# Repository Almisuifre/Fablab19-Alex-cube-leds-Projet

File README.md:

# Fablab19-Alex-cube-leds-Projet
Projet du FbLab19 Cube de leds

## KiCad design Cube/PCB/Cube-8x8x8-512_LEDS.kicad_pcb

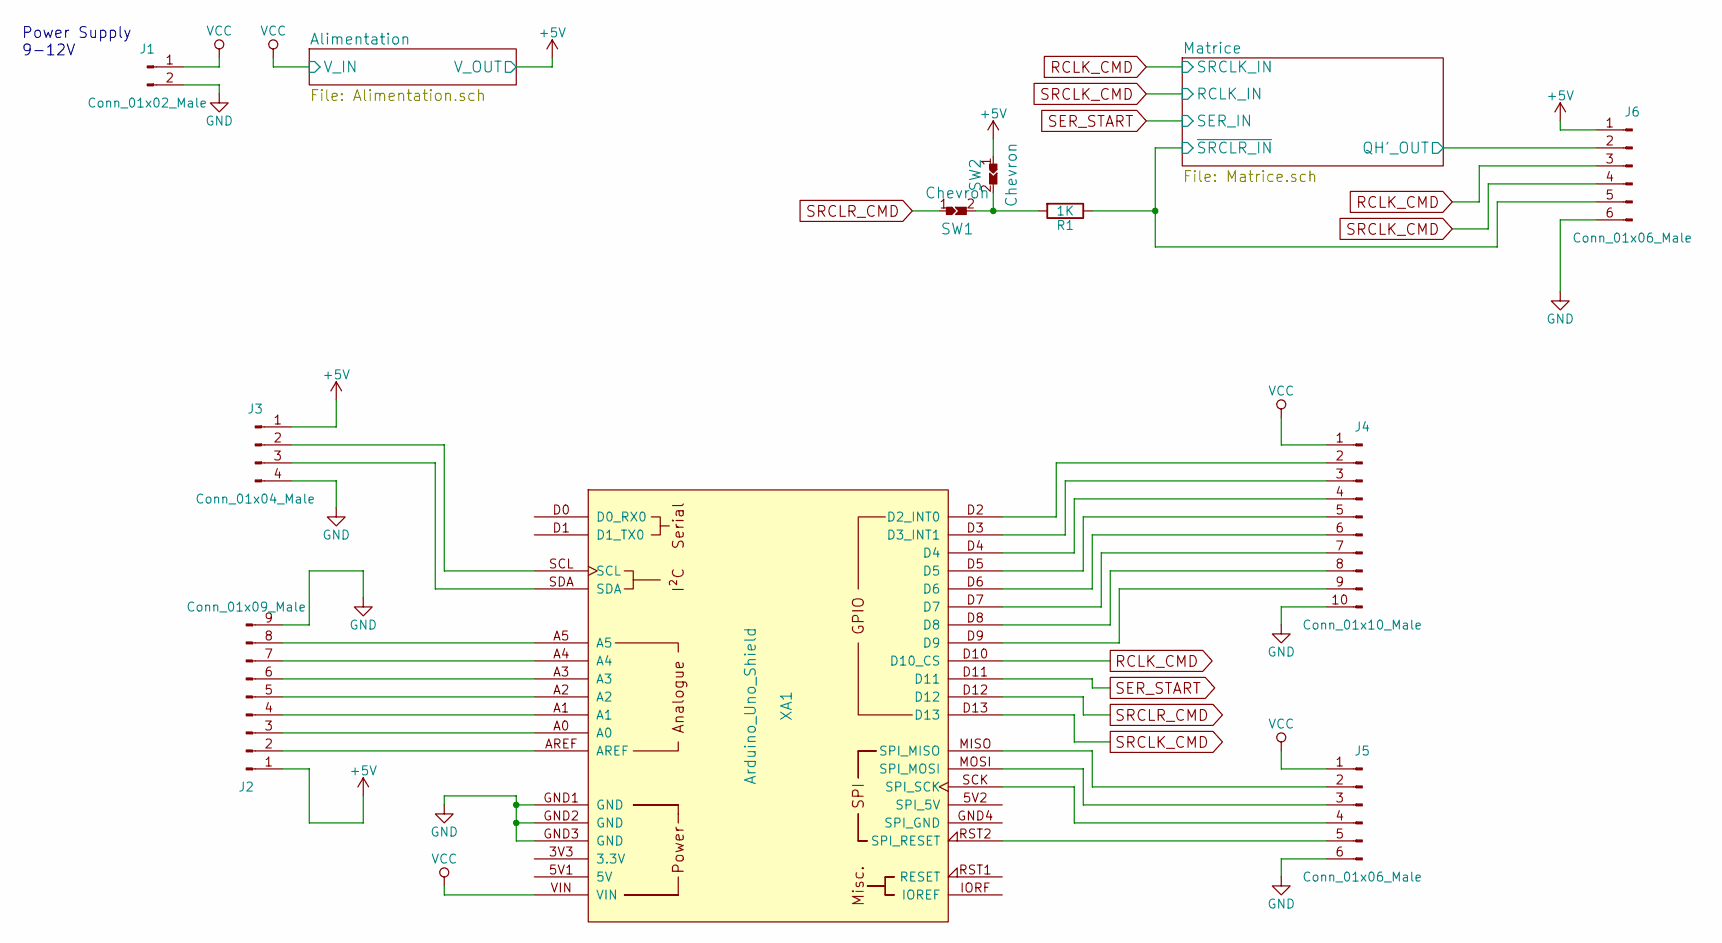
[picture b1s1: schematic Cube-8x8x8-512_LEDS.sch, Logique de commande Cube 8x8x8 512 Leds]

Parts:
J1: Conn_01x02_Male; Connect-2pin
J2: Conn_01x09_Male; Connect-9pin
J3: Conn_01x04_Male; Connect-4pin
J4: Conn_01x10_Male; Connect-10pin
J5, J6: Conn_01x06_Male; Connect-6pin
R1: 1K; R_Axial_Long6.3mm_Dia2.5mm_Pas15.24mm_Horizontal
SW1, SW2: Chevron; Chevron-E1
XA1: Arduino_Uno_Shield

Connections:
+5V: J2.1, J3.1, J6.1, SW2.1; also elsewhere on the board
/Matrice/QH'_OUT: J6.2; also elsewhere on the board
/Matrice/~SRCLR_IN: J6.5, R1.1; also elsewhere on the board
GND: J1.2, J2.9, J3.4, J4.10, J5.6, J6.6, XA1.GND1 (GND), XA1.GND2 (GND), XA1.GND3 (GND); also elsewhere on the board
unnamed: J2.2, XA1.AREF
unnamed: J2.3, XA1.A0
unnamed: J2.4, XA1.A1
unnamed: J2.5, XA1.A2
unnamed: J2.6, XA1.A3
unnamed: J2.7, XA1.A4
unnamed: J2.8, XA1.A5
unnamed: J3.2, XA1.SCL
unnamed: J3.3, XA1.SDA
unnamed: J4.2, XA1.D2 (D2_INT0)
unnamed: J4.3, XA1.D3 (D3_INT1)
unnamed: J4.4, XA1.D4
unnamed: J4.5, XA1.D5
unnamed: J4.6, XA1.D6
unnamed: J4.7, XA1.D7
unnamed: J4.8, XA1.D8
unnamed: J4.9, XA1.D9
unnamed: J5.2, XA1.MISO (SPI_MISO)
unnamed: J5.3, XA1.MOSI (SPI_MOSI)
unnamed: J5.4, XA1.SCK (SPI_SCK)
unnamed: J5.5, XA1.RST2 (SPI_RESET)
unnamed: R1.2, SW1.2, SW2.2
RCLK_CMD: J6.3, XA1.D10 (D10_CS); also elsewhere on the board
SER_START: XA1.D11; also elsewhere on the board
SRCLK_CMD: J6.4, XA1.D13; also elsewhere on the board
SRCLR_CMD: SW1.1, XA1.D12
VCC: J1.1, J4.1, J5.1, XA1.VIN; also elsewhere on the board

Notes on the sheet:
Power Supply 9-12V

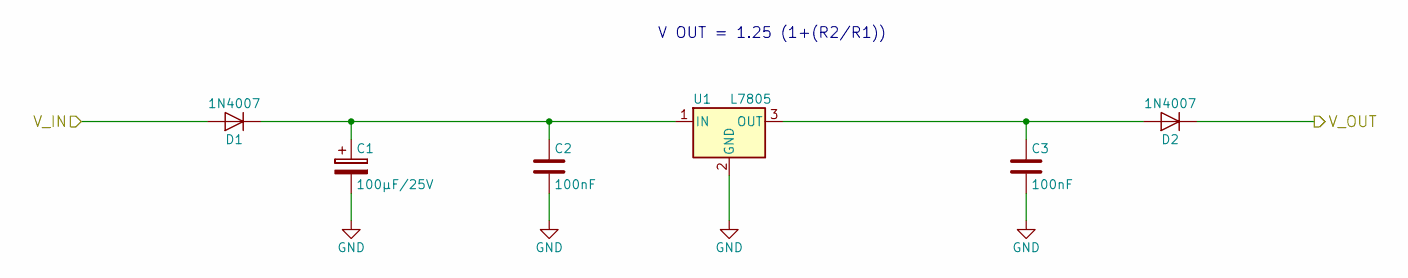
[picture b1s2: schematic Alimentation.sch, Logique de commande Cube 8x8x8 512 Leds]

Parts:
C1: 100µF/25V; CP_Radial_Dia8.0mm_Pas3.50mm
C2, C3: 100nF; C-P_5.08-L_7.5-H_6-P_2.5
D1, D2: 1N4007; D_DO-41_Pas12.70mm_Horizontal
U1: L7805; TO-220_Vertical

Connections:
+5V: D2.1 (K); also elsewhere on the board
GND: C1.2, C2.2, C3.2, U1.2 (GND); also elsewhere on the board
unnamed: C1.1, C2.1, D1.1 (K), U1.1 (IN)
unnamed: C3.1, D2.2 (A), U1.3 (OUT)
VCC: D1.2 (A); also elsewhere on the board

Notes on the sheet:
V OUT = 1.25 (1+(R2/R1))

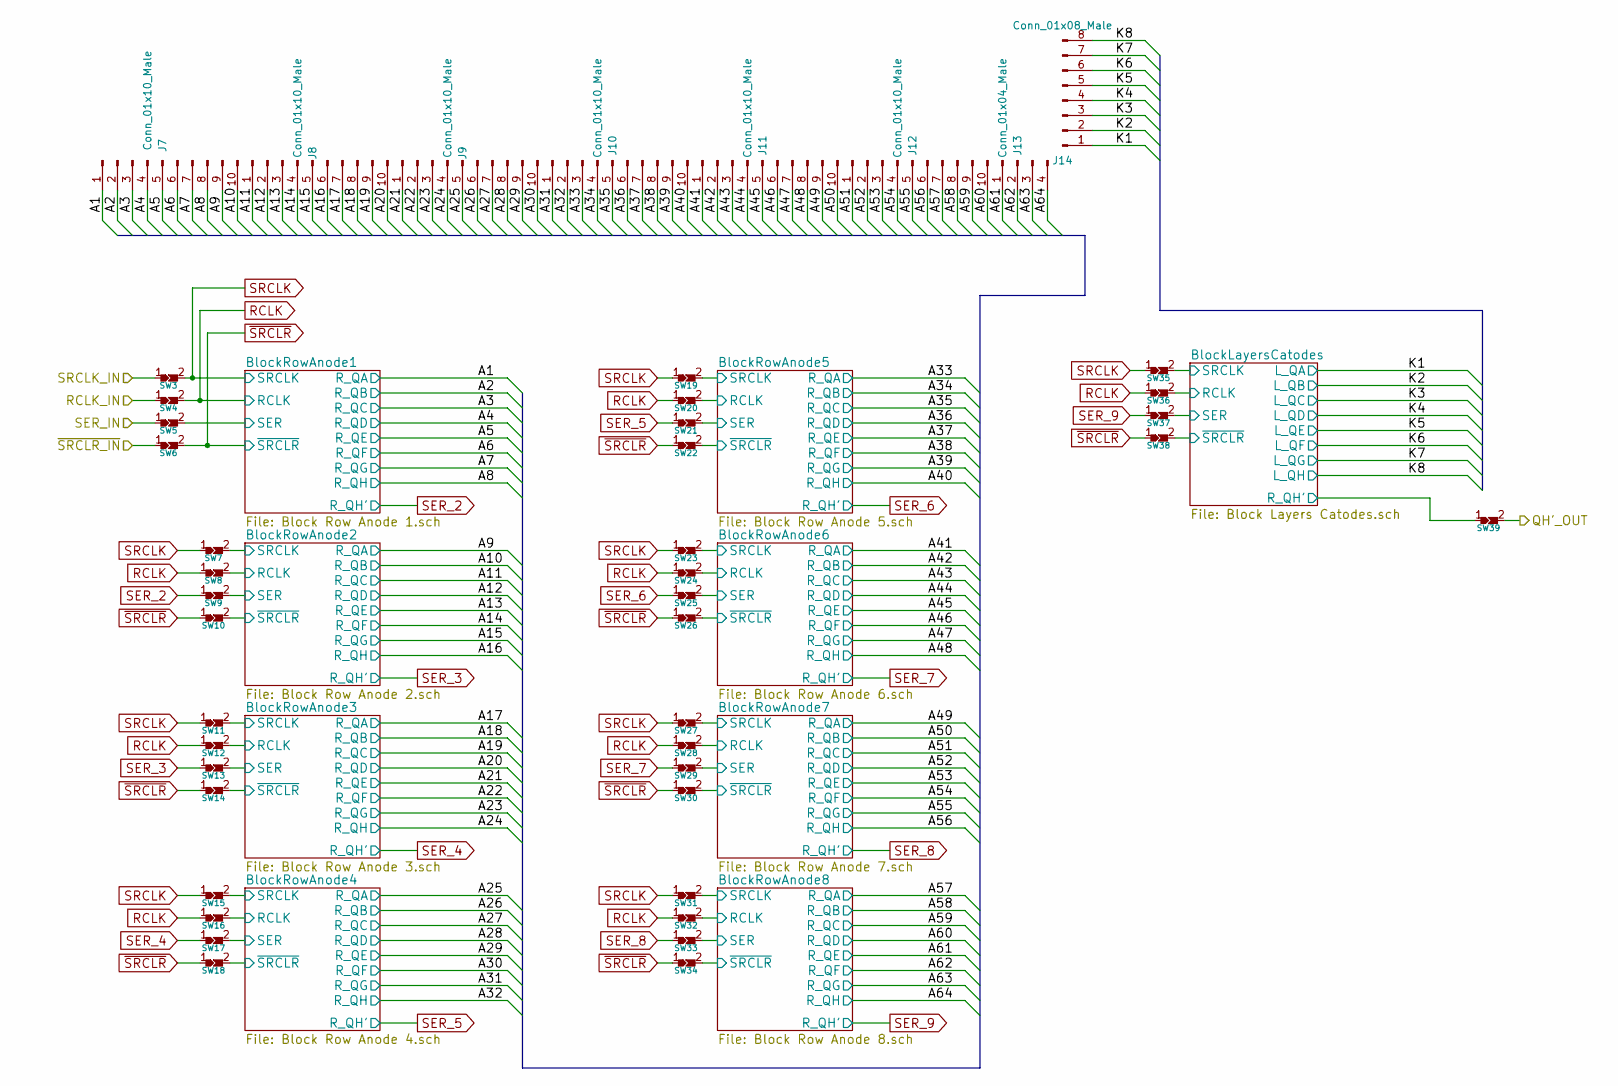
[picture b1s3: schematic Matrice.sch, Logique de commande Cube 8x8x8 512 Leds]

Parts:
J7, J8, J9, J10, J11, J12: Conn_01x10_Male; Connect-10pin
J13: Conn_01x04_Male; Connect-4pin
J14: Conn_01x08_Male; Connect-8pin
SW3, SW4, SW5, SW6, SW7, SW8, SW9, SW10, SW11, SW12, SW13, SW14, SW15, SW16, SW17, SW18, SW19, SW20, SW21, SW22, SW23, SW24, SW25, SW26, SW27, SW28, SW29, SW30, SW31, SW32, SW33, SW34, SW35, SW36, SW37, SW38, SW39: Chevron; Chevron-E1

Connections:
/Matrice/A1: J7.1; also elsewhere on the board
/Matrice/A2: J7.2; also elsewhere on the board
/Matrice/A3: J7.3; also elsewhere on the board
/Matrice/A4: J7.4; also elsewhere on the board
/Matrice/A5: J7.5; also elsewhere on the board
/Matrice/A6: J7.6; also elsewhere on the board
/Matrice/A7: J7.7; also elsewhere on the board
/Matrice/A8: J7.8; also elsewhere on the board
/Matrice/A9: J7.9; also elsewhere on the board
/Matrice/A10: J7.10; also elsewhere on the board
/Matrice/A11: J8.1; also elsewhere on the board
/Matrice/A12: J8.2; also elsewhere on the board
/Matrice/A13: J8.3; also elsewhere on the board
/Matrice/A14: J8.4; also elsewhere on the board
/Matrice/A15: J8.5; also elsewhere on the board
/Matrice/A16: J8.6; also elsewhere on the board
/Matrice/A17: J8.7; also elsewhere on the board
/Matrice/A18: J8.8; also elsewhere on the board
/Matrice/A19: J8.9; also elsewhere on the board
/Matrice/A20: J8.10; also elsewhere on the board
/Matrice/A21: J9.1; also elsewhere on the board
/Matrice/A22: J9.2; also elsewhere on the board
/Matrice/A23: J9.3; also elsewhere on the board
/Matrice/A24: J9.4; also elsewhere on the board
/Matrice/A25: J9.5; also elsewhere on the board
/Matrice/A26: J9.6; also elsewhere on the board
/Matrice/A27: J9.7; also elsewhere on the board
/Matrice/A28: J9.8; also elsewhere on the board
/Matrice/A29: J9.9; also elsewhere on the board
/Matrice/A30: J9.10; also elsewhere on the board
/Matrice/A31: J10.1; also elsewhere on the board
/Matrice/A32: J10.2; also elsewhere on the board
/Matrice/A33: J10.3; also elsewhere on the board
/Matrice/A34: J10.4; also elsewhere on the board
/Matrice/A35: J10.5; also elsewhere on the board
/Matrice/A36: J10.6; also elsewhere on the board
/Matrice/A37: J10.7; also elsewhere on the board
/Matrice/A38: J10.8; also elsewhere on the board
/Matrice/A39: J10.9; also elsewhere on the board
/Matrice/A40: J10.10; also elsewhere on the board
/Matrice/A41: J11.1; also elsewhere on the board
/Matrice/A42: J11.2; also elsewhere on the board
/Matrice/A43: J11.3; also elsewhere on the board
/Matrice/A44: J11.4; also elsewhere on the board
/Matrice/A45: J11.5; also elsewhere on the board
/Matrice/A46: J11.6; also elsewhere on the board
/Matrice/A47: J11.7; also elsewhere on the board
/Matrice/A48: J11.8; also elsewhere on the board
/Matrice/A49: J11.9; also elsewhere on the board
/Matrice/A50: J11.10; also elsewhere on the board
/Matrice/A51: J12.1; also elsewhere on the board
/Matrice/A52: J12.2; also elsewhere on the board
/Matrice/A53: J12.3; also elsewhere on the board
/Matrice/A54: J12.4; also elsewhere on the board
/Matrice/A55: J12.5; also elsewhere on the board
/Matrice/A56: J12.6; also elsewhere on the board
/Matrice/A57: J12.7; also elsewhere on the board
/Matrice/A58: J12.8; also elsewhere on the board
/Matrice/A59: J12.9; also elsewhere on the board
/Matrice/A60: J12.10; also elsewhere on the board
/Matrice/A61: J13.1; also elsewhere on the board
/Matrice/A62: J13.2; also elsewhere on the board
/Matrice/A63: J13.3; also elsewhere on the board
/Matrice/A64: J13.4; also elsewhere on the board
/Matrice/BlockLayersCatodes/RCLK: SW36.2; also elsewhere on the board
/Matrice/BlockLayersCatodes/R_QH': SW39.1; also elsewhere on the board
/Matrice/BlockLayersCatodes/SER: SW37.2; also elsewhere on the board
/Matrice/BlockLayersCatodes/SRCLK: SW35.2; also elsewhere on the board
/Matrice/BlockLayersCatodes/~SRCLR: SW38.2; also elsewhere on the board
/Matrice/BlockRowAnode1/SER: SW5.2; also elsewhere on the board
/Matrice/BlockRowAnode2/RCLK: SW8.2; also elsewhere on the board
/Matrice/BlockRowAnode2/SER: SW9.2; also elsewhere on the board
/Matrice/BlockRowAnode2/SRCLK: SW7.2; also elsewhere on the board
/Matrice/BlockRowAnode2/~SRCLR: SW10.2; also elsewhere on the board
/Matrice/BlockRowAnode3/RCLK: SW12.2; also elsewhere on the board
/Matrice/BlockRowAnode3/SER: SW13.2; also elsewhere on the board
/Matrice/BlockRowAnode3/SRCLK: SW11.2; also elsewhere on the board
/Matrice/BlockRowAnode3/~SRCLR: SW14.2; also elsewhere on the board
/Matrice/BlockRowAnode4/RCLK: SW16.2; also elsewhere on the board
/Matrice/BlockRowAnode4/SER: SW17.2; also elsewhere on the board
/Matrice/BlockRowAnode4/SRCLK: SW15.2; also elsewhere on the board
/Matrice/BlockRowAnode4/~SRCLR: SW18.2; also elsewhere on the board
/Matrice/BlockRowAnode5/RCLK: SW20.2; also elsewhere on the board
/Matrice/BlockRowAnode5/SER: SW21.2; also elsewhere on the board
/Matrice/BlockRowAnode5/SRCLK: SW19.2; also elsewhere on the board
/Matrice/BlockRowAnode5/~SRCLR: SW22.2; also elsewhere on the board
/Matrice/BlockRowAnode6/RCLK: SW24.2; also elsewhere on the board
/Matrice/BlockRowAnode6/SER: SW25.2; also elsewhere on the board
/Matrice/BlockRowAnode6/SRCLK: SW23.2; also elsewhere on the board
/Matrice/BlockRowAnode6/~SRCLR: SW26.2; also elsewhere on the board
/Matrice/BlockRowAnode7/RCLK: SW28.2; also elsewhere on the board
/Matrice/BlockRowAnode7/SER: SW29.2; also elsewhere on the board
/Matrice/BlockRowAnode7/SRCLK: SW27.2; also elsewhere on the board
/Matrice/BlockRowAnode7/~SRCLR: SW30.2; also elsewhere on the board
/Matrice/BlockRowAnode8/RCLK: SW32.2; also elsewhere on the board
/Matrice/BlockRowAnode8/SER: SW33.2; also elsewhere on the board
/Matrice/BlockRowAnode8/SRCLK: SW31.2; also elsewhere on the board
/Matrice/BlockRowAnode8/~SRCLR: SW34.2; also elsewhere on the board
/Matrice/K1: J14.1; also elsewhere on the board
/Matrice/K2: J14.2; also elsewhere on the board
/Matrice/K3: J14.3; also elsewhere on the board
/Matrice/K4: J14.4; also elsewhere on the board
/Matrice/K5: J14.5; also elsewhere on the board
/Matrice/K6: J14.6; also elsewhere on the board
/Matrice/K7: J14.7; also elsewhere on the board
/Matrice/K8: J14.8; also elsewhere on the board
/Matrice/QH'_OUT: SW39.2; also elsewhere on the board
/Matrice/~SRCLR_IN: SW6.1; also elsewhere on the board
RCLK: SW4.2, SW8.1, SW12.1, SW16.1, SW20.1, SW24.1, SW28.1, SW32.1, SW36.1; also elsewhere on the board
RCLK_CMD: SW3.1; also elsewhere on the board
SER_2: SW9.1; also elsewhere on the board
SER_3: SW13.1; also elsewhere on the board
SER_4: SW17.1; also elsewhere on the board
SER_5: SW21.1; also elsewhere on the board
SER_6: SW25.1; also elsewhere on the board
SER_7: SW29.1; also elsewhere on the board
SER_8: SW33.1; also elsewhere on the board
SER_9: SW37.1; also elsewhere on the board
SER_START: SW5.1; also elsewhere on the board
SRCLK: SW3.2, SW7.1, SW11.1, SW15.1, SW19.1, SW23.1, SW27.1, SW31.1, SW35.1; also elsewhere on the board
SRCLK_CMD: SW4.1; also elsewhere on the board
~SRCLR: SW6.2, SW10.1, SW14.1, SW18.1, SW22.1, SW26.1, SW30.1, SW34.1, SW38.1; also elsewhere on the board

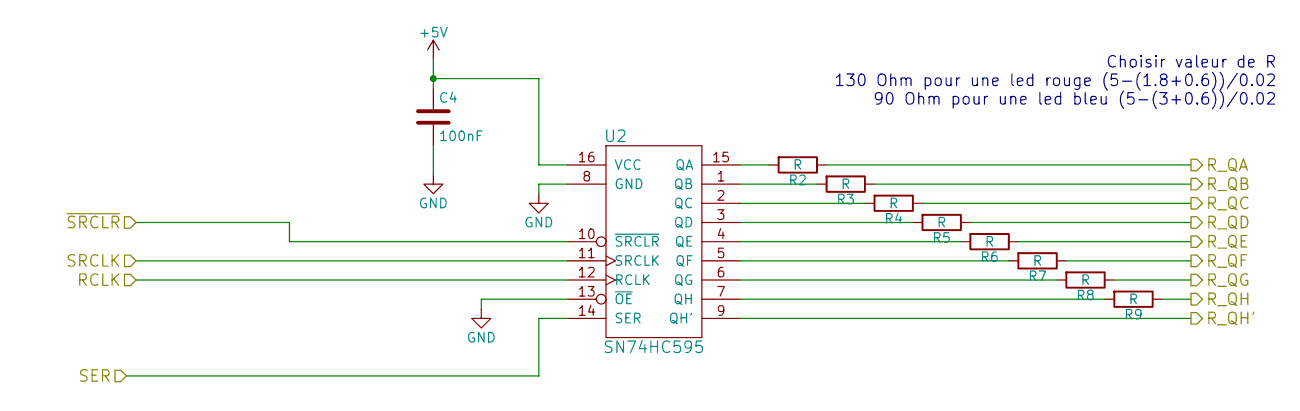
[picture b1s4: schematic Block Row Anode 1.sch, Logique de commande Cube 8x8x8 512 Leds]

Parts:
C4: 100nF; C-P_5.08-L_7.5-H_6-P_2.5
R2, R3, R4, R5, R6, R7, R8, R9: R; R_Axial_Long6.3mm_Dia2.5mm_Pas15.24mm_Horizontal
U2: SN74HC595; DIP-16_W7.62mm_LongPads

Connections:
+5V: C4.1, U2.16 (VCC); also elsewhere on the board
/Matrice/A1: R2.1; also elsewhere on the board
/Matrice/A2: R3.1; also elsewhere on the board
/Matrice/A3: R4.1; also elsewhere on the board
/Matrice/A4: R5.1; also elsewhere on the board
/Matrice/A5: R6.1; also elsewhere on the board
/Matrice/A6: R7.1; also elsewhere on the board
/Matrice/A7: R8.1; also elsewhere on the board
/Matrice/A8: R9.1; also elsewhere on the board
/Matrice/BlockRowAnode1/SER: U2.14 (SER); also elsewhere on the board
GND: C4.2, U2.8 (GND), U2.13 (~OE); also elsewhere on the board
unnamed: R2.2, U2.15 (QA)
unnamed: R3.2, U2.1 (QB)
unnamed: R4.2, U2.2 (QC)
unnamed: R5.2, U2.3 (QD)
unnamed: R6.2, U2.4 (QE)
unnamed: R7.2, U2.5 (QF)
unnamed: R8.2, U2.6 (QG)
unnamed: R9.2, U2.7 (QH)
RCLK: U2.12 (RCLK); also elsewhere on the board
SER_2: U2.9 (QH'); also elsewhere on the board
SRCLK: U2.11 (SRCLK); also elsewhere on the board
~SRCLR: U2.10 (~SRCLR); also elsewhere on the board

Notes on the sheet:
Choisir valeur de R 130 Ohm pour une led rouge (5-(1.8+0.6))/0.02 90 Ohm pour une led bleu (5-(3+0.6))/0.02

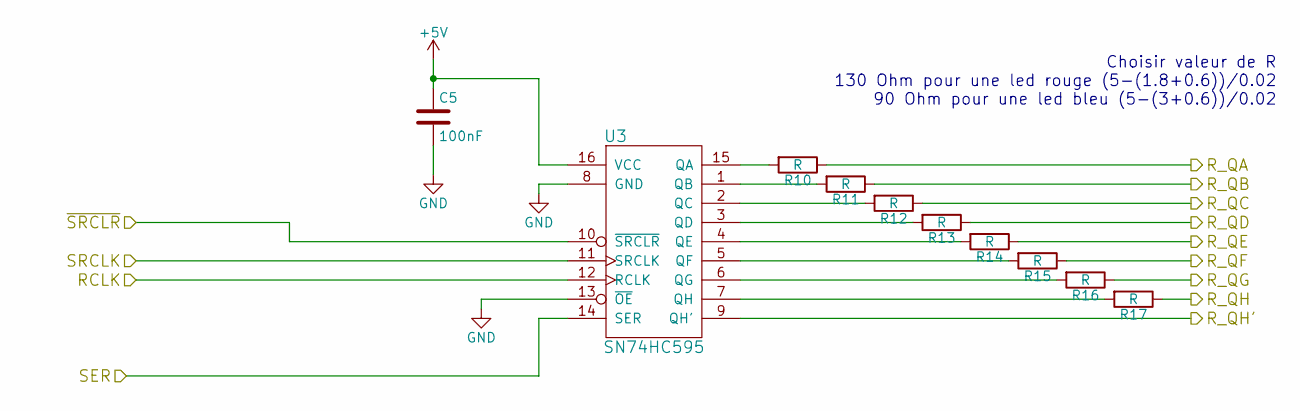
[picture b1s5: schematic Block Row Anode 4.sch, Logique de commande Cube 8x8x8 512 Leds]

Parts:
C5: 100nF; C-P_5.08-L_7.5-H_6-P_2.5
R10, R11, R12, R13, R14, R15, R16, R17: R; R_Axial_Long6.3mm_Dia2.5mm_Pas15.24mm_Horizontal
U3: SN74HC595; DIP-16_W7.62mm_LongPads

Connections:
+5V: C5.1, U3.16 (VCC); also elsewhere on the board
/Matrice/A25: R10.1; also elsewhere on the board
/Matrice/A26: R11.1; also elsewhere on the board
/Matrice/A27: R12.1; also elsewhere on the board
/Matrice/A28: R13.1; also elsewhere on the board
/Matrice/A29: R14.1; also elsewhere on the board
/Matrice/A30: R15.1; also elsewhere on the board
/Matrice/A31: R16.1; also elsewhere on the board
/Matrice/A32: R17.1; also elsewhere on the board
/Matrice/BlockRowAnode4/RCLK: U3.12 (RCLK); also elsewhere on the board
/Matrice/BlockRowAnode4/SER: U3.14 (SER); also elsewhere on the board
/Matrice/BlockRowAnode4/SRCLK: U3.11 (SRCLK); also elsewhere on the board
/Matrice/BlockRowAnode4/~SRCLR: U3.10 (~SRCLR); also elsewhere on the board
GND: C5.2, U3.8 (GND), U3.13 (~OE); also elsewhere on the board
unnamed: R10.2, U3.15 (QA)
unnamed: R11.2, U3.1 (QB)
unnamed: R12.2, U3.2 (QC)
unnamed: R13.2, U3.3 (QD)
unnamed: R14.2, U3.4 (QE)
unnamed: R15.2, U3.5 (QF)
unnamed: R16.2, U3.6 (QG)
unnamed: R17.2, U3.7 (QH)
SER_5: U3.9 (QH'); also elsewhere on the board

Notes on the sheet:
Choisir valeur de R 130 Ohm pour une led rouge (5-(1.8+0.6))/0.02 90 Ohm pour une led bleu (5-(3+0.6))/0.02

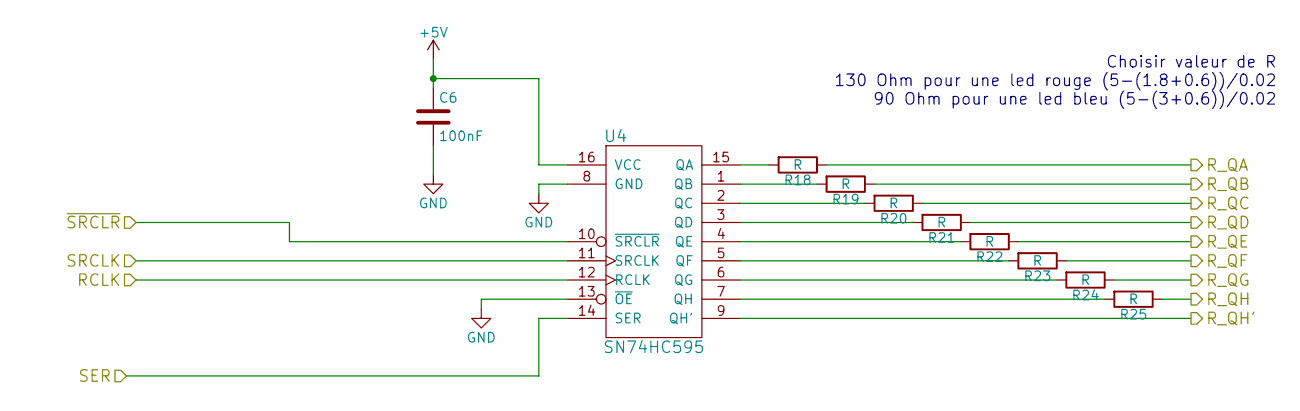
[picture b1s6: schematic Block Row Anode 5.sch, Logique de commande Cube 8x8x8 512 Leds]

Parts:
C6: 100nF; C-P_5.08-L_7.5-H_6-P_2.5
R18, R19, R20, R21, R22, R23, R24, R25: R; R_Axial_Long6.3mm_Dia2.5mm_Pas15.24mm_Horizontal
U4: SN74HC595; DIP-16_W7.62mm_LongPads

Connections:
+5V: C6.1, U4.16 (VCC); also elsewhere on the board
/Matrice/A33: R18.1; also elsewhere on the board
/Matrice/A34: R19.1; also elsewhere on the board
/Matrice/A35: R20.1; also elsewhere on the board
/Matrice/A36: R21.1; also elsewhere on the board
/Matrice/A37: R22.1; also elsewhere on the board
/Matrice/A38: R23.1; also elsewhere on the board
/Matrice/A39: R24.1; also elsewhere on the board
/Matrice/A40: R25.1; also elsewhere on the board
/Matrice/BlockRowAnode5/RCLK: U4.12 (RCLK); also elsewhere on the board
/Matrice/BlockRowAnode5/SER: U4.14 (SER); also elsewhere on the board
/Matrice/BlockRowAnode5/SRCLK: U4.11 (SRCLK); also elsewhere on the board
/Matrice/BlockRowAnode5/~SRCLR: U4.10 (~SRCLR); also elsewhere on the board
GND: C6.2, U4.8 (GND), U4.13 (~OE); also elsewhere on the board
unnamed: R18.2, U4.15 (QA)
unnamed: R19.2, U4.1 (QB)
unnamed: R20.2, U4.2 (QC)
unnamed: R21.2, U4.3 (QD)
unnamed: R22.2, U4.4 (QE)
unnamed: R23.2, U4.5 (QF)
unnamed: R24.2, U4.6 (QG)
unnamed: R25.2, U4.7 (QH)
SER_6: U4.9 (QH'); also elsewhere on the board

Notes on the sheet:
Choisir valeur de R 130 Ohm pour une led rouge (5-(1.8+0.6))/0.02 90 Ohm pour une led bleu (5-(3+0.6))/0.02

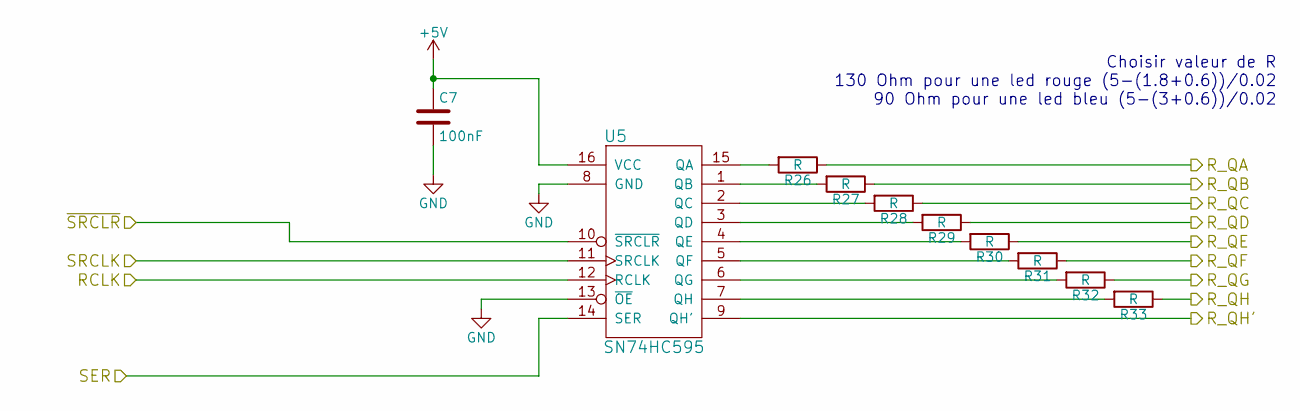
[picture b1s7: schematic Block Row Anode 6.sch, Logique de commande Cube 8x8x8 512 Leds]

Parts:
C7: 100nF; C-P_5.08-L_7.5-H_6-P_2.5
R26, R27, R28, R29, R30, R31, R32, R33: R; R_Axial_Long6.3mm_Dia2.5mm_Pas15.24mm_Horizontal
U5: SN74HC595; DIP-16_W7.62mm_LongPads

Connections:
+5V: C7.1, U5.16 (VCC); also elsewhere on the board
/Matrice/A41: R26.1; also elsewhere on the board
/Matrice/A42: R27.1; also elsewhere on the board
/Matrice/A43: R28.1; also elsewhere on the board
/Matrice/A44: R29.1; also elsewhere on the board
/Matrice/A45: R30.1; also elsewhere on the board
/Matrice/A46: R31.1; also elsewhere on the board
/Matrice/A47: R32.1; also elsewhere on the board
/Matrice/A48: R33.1; also elsewhere on the board
/Matrice/BlockRowAnode6/RCLK: U5.12 (RCLK); also elsewhere on the board
/Matrice/BlockRowAnode6/SER: U5.14 (SER); also elsewhere on the board
/Matrice/BlockRowAnode6/SRCLK: U5.11 (SRCLK); also elsewhere on the board
/Matrice/BlockRowAnode6/~SRCLR: U5.10 (~SRCLR); also elsewhere on the board
GND: C7.2, U5.8 (GND), U5.13 (~OE); also elsewhere on the board
unnamed: R26.2, U5.15 (QA)
unnamed: R27.2, U5.1 (QB)
unnamed: R28.2, U5.2 (QC)
unnamed: R29.2, U5.3 (QD)
unnamed: R30.2, U5.4 (QE)
unnamed: R31.2, U5.5 (QF)
unnamed: R32.2, U5.6 (QG)
unnamed: R33.2, U5.7 (QH)
SER_7: U5.9 (QH'); also elsewhere on the board

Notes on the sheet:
Choisir valeur de R 130 Ohm pour une led rouge (5-(1.8+0.6))/0.02 90 Ohm pour une led bleu (5-(3+0.6))/0.02

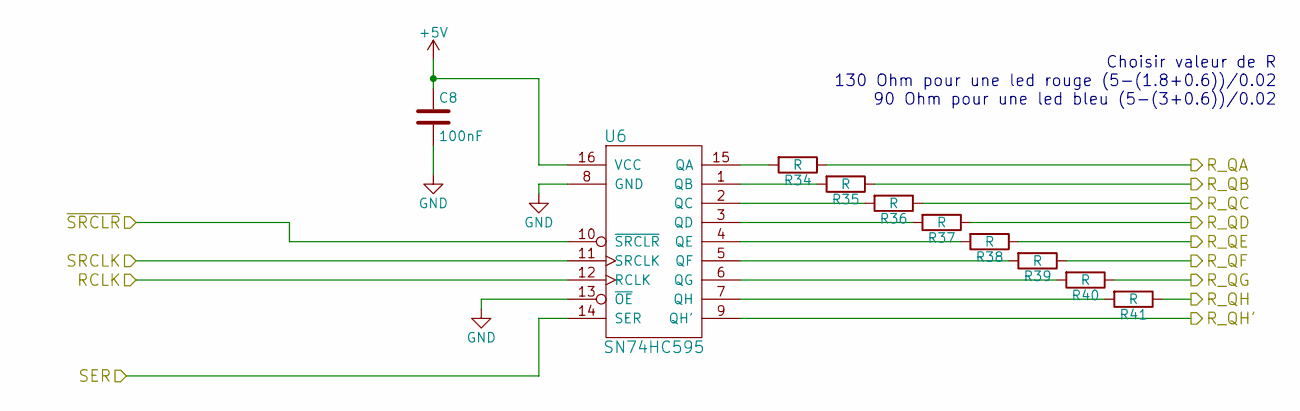
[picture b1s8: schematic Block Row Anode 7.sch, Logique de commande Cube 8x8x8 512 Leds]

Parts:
C8: 100nF; C-P_5.08-L_7.5-H_6-P_2.5
R34, R35, R36, R37, R38, R39, R40, R41: R; R_Axial_Long6.3mm_Dia2.5mm_Pas15.24mm_Horizontal
U6: SN74HC595; DIP-16_W7.62mm_LongPads

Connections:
+5V: C8.1, U6.16 (VCC); also elsewhere on the board
/Matrice/A49: R34.1; also elsewhere on the board
/Matrice/A50: R35.1; also elsewhere on the board
/Matrice/A51: R36.1; also elsewhere on the board
/Matrice/A52: R37.1; also elsewhere on the board
/Matrice/A53: R38.1; also elsewhere on the board
/Matrice/A54: R39.1; also elsewhere on the board
/Matrice/A55: R40.1; also elsewhere on the board
/Matrice/A56: R41.1; also elsewhere on the board
/Matrice/BlockRowAnode7/RCLK: U6.12 (RCLK); also elsewhere on the board
/Matrice/BlockRowAnode7/SER: U6.14 (SER); also elsewhere on the board
/Matrice/BlockRowAnode7/SRCLK: U6.11 (SRCLK); also elsewhere on the board
/Matrice/BlockRowAnode7/~SRCLR: U6.10 (~SRCLR); also elsewhere on the board
GND: C8.2, U6.8 (GND), U6.13 (~OE); also elsewhere on the board
unnamed: R34.2, U6.15 (QA)
unnamed: R35.2, U6.1 (QB)
unnamed: R36.2, U6.2 (QC)
unnamed: R37.2, U6.3 (QD)
unnamed: R38.2, U6.4 (QE)
unnamed: R39.2, U6.5 (QF)
unnamed: R40.2, U6.6 (QG)
unnamed: R41.2, U6.7 (QH)
SER_8: U6.9 (QH'); also elsewhere on the board

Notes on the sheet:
Choisir valeur de R 130 Ohm pour une led rouge (5-(1.8+0.6))/0.02 90 Ohm pour une led bleu (5-(3+0.6))/0.02

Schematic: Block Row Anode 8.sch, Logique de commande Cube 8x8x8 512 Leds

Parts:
C9: 100nF; C-P_5.08-L_7.5-H_6-P_2.5
R42, R43, R44, R45, R46, R47, R48, R49: R; R_Axial_Long6.3mm_Dia2.5mm_Pas15.24mm_Horizontal
U7: SN74HC595; DIP-16_W7.62mm_LongPads

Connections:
+5V: C9.1, U7.16 (VCC); also elsewhere on the board
/Matrice/A57: R42.1; also elsewhere on the board
/Matrice/A58: R43.1; also elsewhere on the board
/Matrice/A59: R44.1; also elsewhere on the board
/Matrice/A60: R45.1; also elsewhere on the board
/Matrice/A61: R46.1; also elsewhere on the board
/Matrice/A62: R47.1; also elsewhere on the board
/Matrice/A63: R48.1; also elsewhere on the board
/Matrice/A64: R49.1; also elsewhere on the board
/Matrice/BlockRowAnode8/RCLK: U7.12 (RCLK); also elsewhere on the board
/Matrice/BlockRowAnode8/SER: U7.14 (SER); also elsewhere on the board
/Matrice/BlockRowAnode8/SRCLK: U7.11 (SRCLK); also elsewhere on the board
/Matrice/BlockRowAnode8/~SRCLR: U7.10 (~SRCLR); also elsewhere on the board
GND: C9.2, U7.8 (GND), U7.13 (~OE); also elsewhere on the board
unnamed: R42.2, U7.15 (QA)
unnamed: R43.2, U7.1 (QB)
unnamed: R44.2, U7.2 (QC)
unnamed: R45.2, U7.3 (QD)
unnamed: R46.2, U7.4 (QE)
unnamed: R47.2, U7.5 (QF)
unnamed: R48.2, U7.6 (QG)
unnamed: R49.2, U7.7 (QH)
SER_9: U7.9 (QH'); also elsewhere on the board

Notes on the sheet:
Choisir valeur de R 130 Ohm pour une led rouge (5-(1.8+0.6))/0.02 90 Ohm pour une led bleu (5-(3+0.6))/0.02

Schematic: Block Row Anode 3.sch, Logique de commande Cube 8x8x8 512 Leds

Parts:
C10: 100nF; C-P_5.08-L_7.5-H_6-P_2.5
R50, R51, R52, R53, R54, R55, R56, R57: R; R_Axial_Long6.3mm_Dia2.5mm_Pas15.24mm_Horizontal
U8: SN74HC595; DIP-16_W7.62mm_LongPads

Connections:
+5V: C10.1, U8.16 (VCC); also elsewhere on the board
/Matrice/A17: R50.1; also elsewhere on the board
/Matrice/A18: R51.1; also elsewhere on the board
/Matrice/A19: R52.1; also elsewhere on the board
/Matrice/A20: R53.1; also elsewhere on the board
/Matrice/A21: R54.1; also elsewhere on the board
/Matrice/A22: R55.1; also elsewhere on the board
/Matrice/A23: R56.1; also elsewhere on the board
/Matrice/A24: R57.1; also elsewhere on the board
/Matrice/BlockRowAnode3/RCLK: U8.12 (RCLK); also elsewhere on the board
/Matrice/BlockRowAnode3/SER: U8.14 (SER); also elsewhere on the board
/Matrice/BlockRowAnode3/SRCLK: U8.11 (SRCLK); also elsewhere on the board
/Matrice/BlockRowAnode3/~SRCLR: U8.10 (~SRCLR); also elsewhere on the board
GND: C10.2, U8.8 (GND), U8.13 (~OE); also elsewhere on the board
unnamed: R50.2, U8.15 (QA)
unnamed: R51.2, U8.1 (QB)
unnamed: R52.2, U8.2 (QC)
unnamed: R53.2, U8.3 (QD)
unnamed: R54.2, U8.4 (QE)
unnamed: R55.2, U8.5 (QF)
unnamed: R56.2, U8.6 (QG)
unnamed: R57.2, U8.7 (QH)
SER_4: U8.9 (QH'); also elsewhere on the board

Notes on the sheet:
Choisir valeur de R 130 Ohm pour une led rouge (5-(1.8+0.6))/0.02 90 Ohm pour une led bleu (5-(3+0.6))/0.02

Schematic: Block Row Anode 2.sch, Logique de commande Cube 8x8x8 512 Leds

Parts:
C11: 100nF; C-P_5.08-L_7.5-H_6-P_2.5
R58, R59, R60, R61, R62, R63, R64, R65: R; R_Axial_Long6.3mm_Dia2.5mm_Pas15.24mm_Horizontal
U9: SN74HC595; DIP-16_W7.62mm_LongPads

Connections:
+5V: C11.1, U9.16 (VCC); also elsewhere on the board
/Matrice/A9: R58.1; also elsewhere on the board
/Matrice/A10: R59.1; also elsewhere on the board
/Matrice/A11: R60.1; also elsewhere on the board
/Matrice/A12: R61.1; also elsewhere on the board
/Matrice/A13: R62.1; also elsewhere on the board
/Matrice/A14: R63.1; also elsewhere on the board
/Matrice/A15: R64.1; also elsewhere on the board
/Matrice/A16: R65.1; also elsewhere on the board
/Matrice/BlockRowAnode2/RCLK: U9.12 (RCLK); also elsewhere on the board
/Matrice/BlockRowAnode2/SER: U9.14 (SER); also elsewhere on the board
/Matrice/BlockRowAnode2/SRCLK: U9.11 (SRCLK); also elsewhere on the board
/Matrice/BlockRowAnode2/~SRCLR: U9.10 (~SRCLR); also elsewhere on the board
GND: C11.2, U9.8 (GND), U9.13 (~OE); also elsewhere on the board
unnamed: R58.2, U9.15 (QA)
unnamed: R59.2, U9.1 (QB)
unnamed: R60.2, U9.2 (QC)
unnamed: R61.2, U9.3 (QD)
unnamed: R62.2, U9.4 (QE)
unnamed: R63.2, U9.5 (QF)
unnamed: R64.2, U9.6 (QG)
unnamed: R65.2, U9.7 (QH)
SER_3: U9.9 (QH'); also elsewhere on the board

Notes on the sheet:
Choisir valeur de R 130 Ohm pour une led rouge (5-(1.8+0.6))/0.02 90 Ohm pour une led bleu (5-(3+0.6))/0.02

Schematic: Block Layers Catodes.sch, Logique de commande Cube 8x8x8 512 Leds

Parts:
C12: 100nF; C-P_5.08-L_7.5-H_6-P_2.5
Q1, Q2, Q3, Q4, Q5, Q6, Q7, Q8: PN2222A; TO-92_Inline_Narrow_Oval
R66, R67, R68, R69, R70, R71, R72, R73: 1,1K; R_Axial_Long6.3mm_Dia2.5mm_Pas15.24mm_Horizontal
U10: SN74HC595; DIP-16_W7.62mm_LongPads

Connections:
+5V: C12.1, U10.16 (VCC); also elsewhere on the board
/Matrice/BlockLayersCatodes/RCLK: U10.12 (RCLK); also elsewhere on the board
/Matrice/BlockLayersCatodes/R_QH': U10.9 (QH'); also elsewhere on the board
/Matrice/BlockLayersCatodes/SER: U10.14 (SER); also elsewhere on the board
/Matrice/BlockLayersCatodes/SRCLK: U10.11 (SRCLK); also elsewhere on the board
/Matrice/BlockLayersCatodes/~SRCLR: U10.10 (~SRCLR); also elsewhere on the board
/Matrice/K1: Q1.3 (C); also elsewhere on the board
/Matrice/K2: Q2.3 (C); also elsewhere on the board
/Matrice/K3: Q3.3 (C); also elsewhere on the board
/Matrice/K4: Q4.3 (C); also elsewhere on the board
/Matrice/K5: Q5.3 (C); also elsewhere on the board
/Matrice/K6: Q6.3 (C); also elsewhere on the board
/Matrice/K7: Q7.3 (C); also elsewhere on the board
/Matrice/K8: Q8.3 (C); also elsewhere on the board
GND: C12.2, Q1.1 (E), Q2.1 (E), Q3.1 (E), Q4.1 (E), Q5.1 (E), Q6.1 (E), Q7.1 (E), Q8.1 (E), U10.8 (GND), U10.13 (~OE); also elsewhere on the board
unnamed: Q1.2 (B), R66.2
unnamed: Q2.2 (B), R67.2
unnamed: Q3.2 (B), R68.2
unnamed: Q4.2 (B), R69.2
unnamed: Q5.2 (B), R70.2
unnamed: Q6.2 (B), R71.2
unnamed: Q7.2 (B), R72.2
unnamed: Q8.2 (B), R73.2
unnamed: R66.1, U10.15 (QA)
unnamed: R67.1, U10.1 (QB)
unnamed: R68.1, U10.2 (QC)
unnamed: R69.1, U10.3 (QD)
unnamed: R70.1, U10.4 (QE)
unnamed: R71.1, U10.5 (QF)
unnamed: R72.1, U10.6 (QG)
unnamed: R73.1, U10.7 (QH)

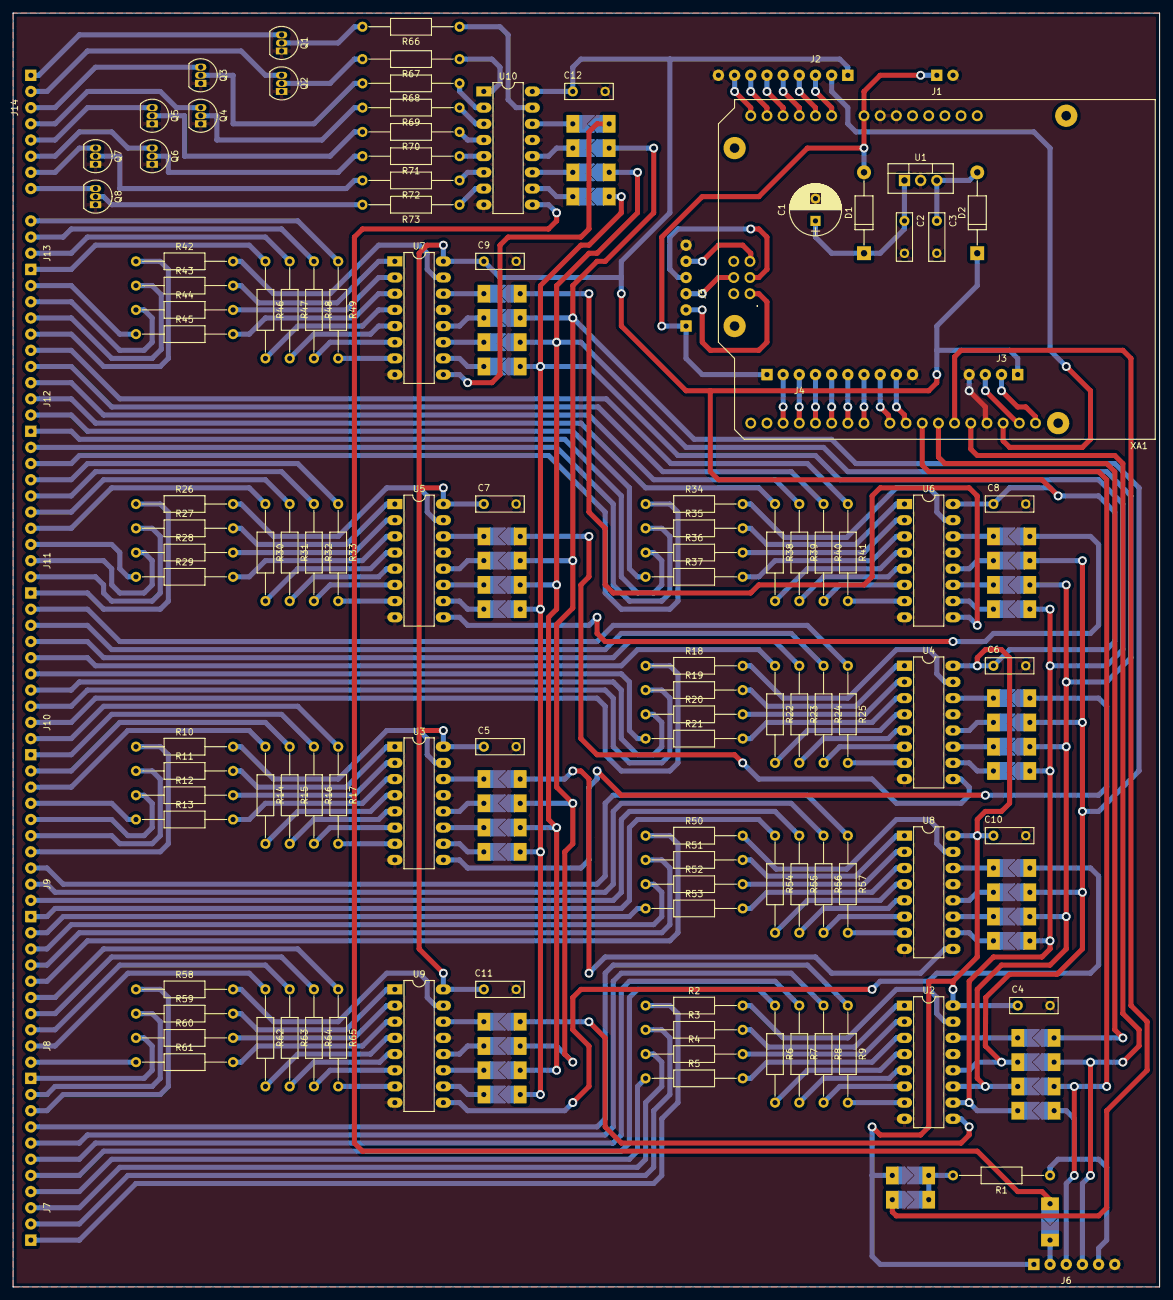
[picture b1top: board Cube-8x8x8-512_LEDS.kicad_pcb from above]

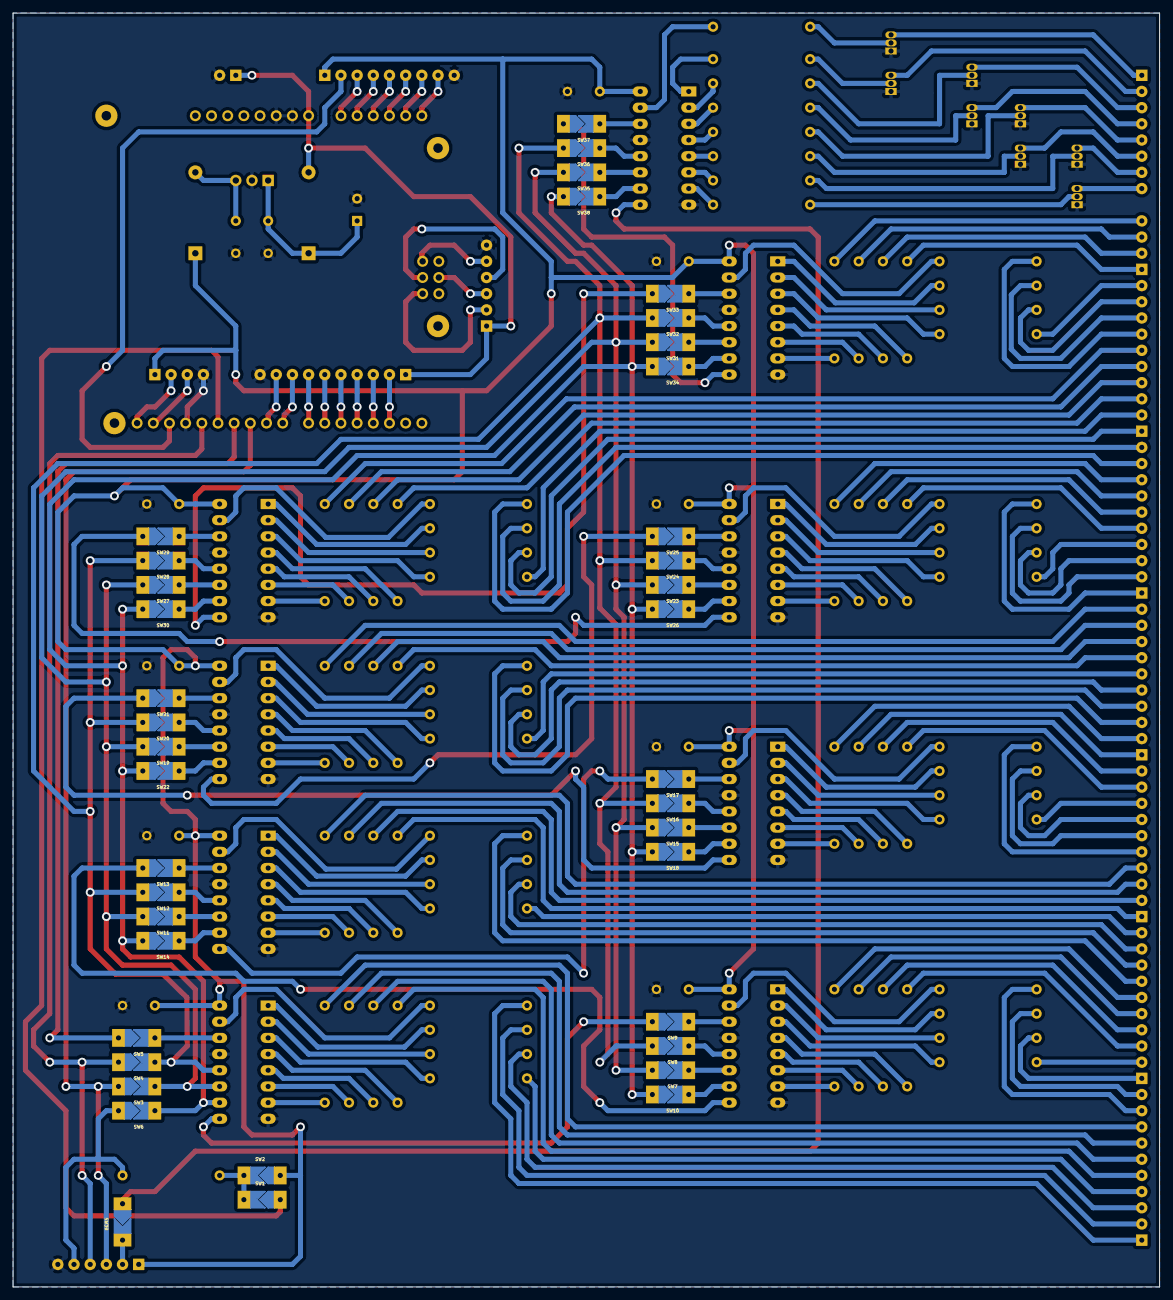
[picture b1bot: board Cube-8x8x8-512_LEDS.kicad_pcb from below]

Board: 2 copper layers, 180.0 x 200.0 mm, 159 parts (39 on the bottom side), 230 nets.
